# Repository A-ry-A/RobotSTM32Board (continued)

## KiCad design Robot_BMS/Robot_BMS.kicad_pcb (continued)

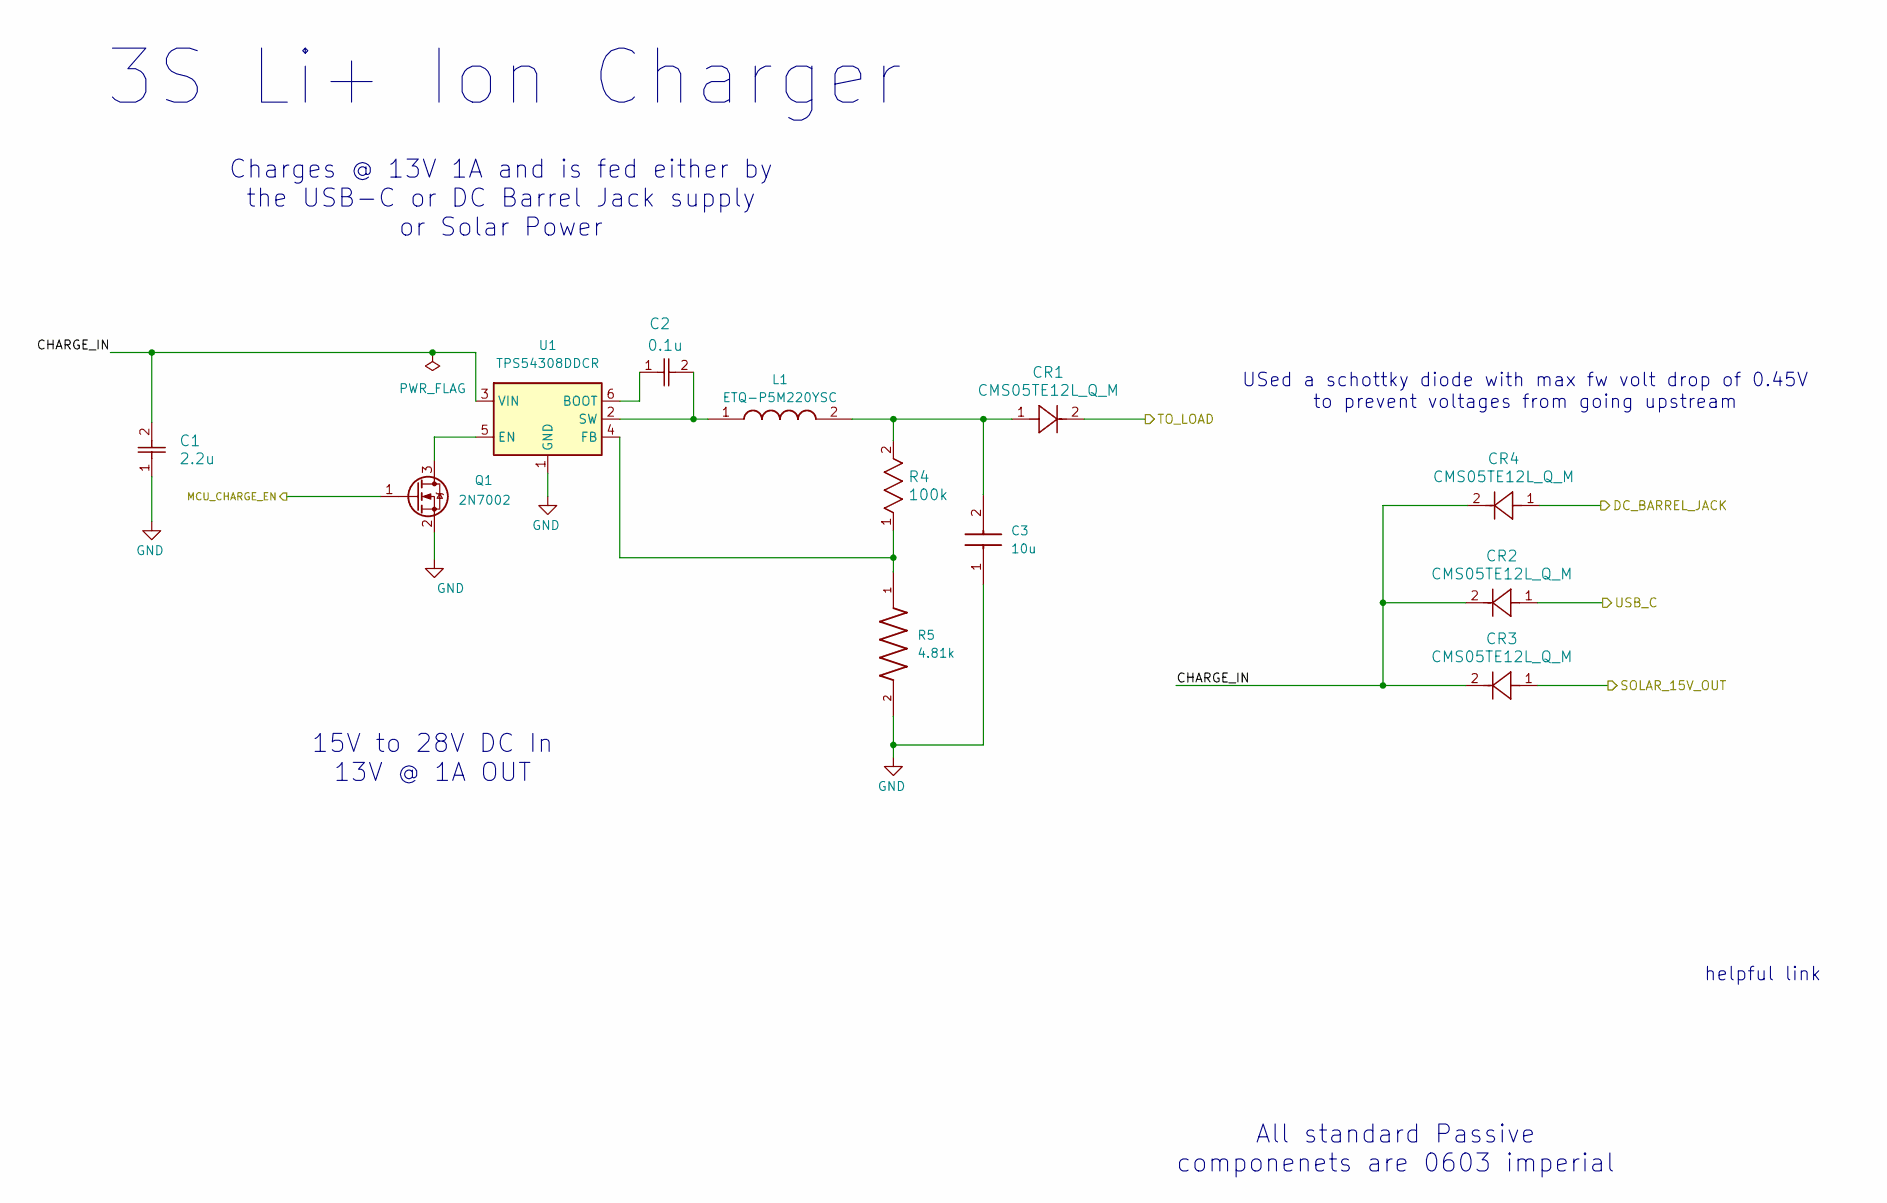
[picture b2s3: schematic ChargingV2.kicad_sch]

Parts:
C1: 2.2u; CAP_GRM188R61H225KE11__MUR; Manufacturer_Part_Number GRM188R61H225KE11D
C2: 0.1u; CAPC17595_87N_KEM; Manufacturer_Part_Number C0603C104K5RACAUTO
C3: 10u; CAPC1608X90N; Mouser Part Number 187-CL10A106MA8NRNC
CR1, CR2, CR3, CR4: CMS05TE12L_Q_M; M-FLAT_TOS; Manufacturer_Part_Number CMS05TE12L_Q_M
L1: ETQ-P5M220YSC; ETQP5M220YSC; Manufacturer_Part_Number ETQ-P5M220YSC
Q1: 2N7002; SOT-23; Manufacturer_Part_Number 2N7002 H6327
R4: 100k; RES_R0603_ROM; Manufacturer_Part_Number ESR03EZPF1003
R5: 4.81k; RESC1608X55N; Manufacturer_Part_Number RN73H1JTTD4811B25
U1: TPS54308DDCR; SOT-23-6; Manufacturer_Part_Number TPS54308DDCR

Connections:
/Charging Circuit/CHARGE_IN: C1.2, CR2.2, CR3.2, CR4.2, U1.3 (VIN)
/Charging Circuit/DC_BARREL_JACK: CR4.1; also elsewhere on the board
/Charging Circuit/MCU_CHARGE_EN: Q1.1 (G); also elsewhere on the board
/Charging Circuit/SOLAR_15V_OUT: CR3.1; also elsewhere on the board
/Charging Circuit/TO_LOAD: CR1.2
/Charging Circuit/USB_C: CR2.1; also elsewhere on the board
GND: C1.1, C3.1, Q1.2 (S), R5.2, U1.1 (GND); also elsewhere on the board
unnamed: C3.2, CR1.1, L1.2, R4.2
unnamed: Q1.3 (D), U1.5 (EN)
unnamed: C2.1, U1.6 (BOOT)
unnamed: R4.1, R5.1, U1.4 (FB)
unnamed: C2.2, L1.1, U1.2 (SW)

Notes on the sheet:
helpful link
Charges @ 13V 1A and is fed either by the USB-C or DC Barrel Jack supply or Solar Power
USed a schottky diode with max fw volt drop of 0.45V to prevent voltages from going upstream
15V to 28V DC In 13V @ 1A OUT
3S Li+ Ion Charger
All standard Passive componenets are 0603 imperial

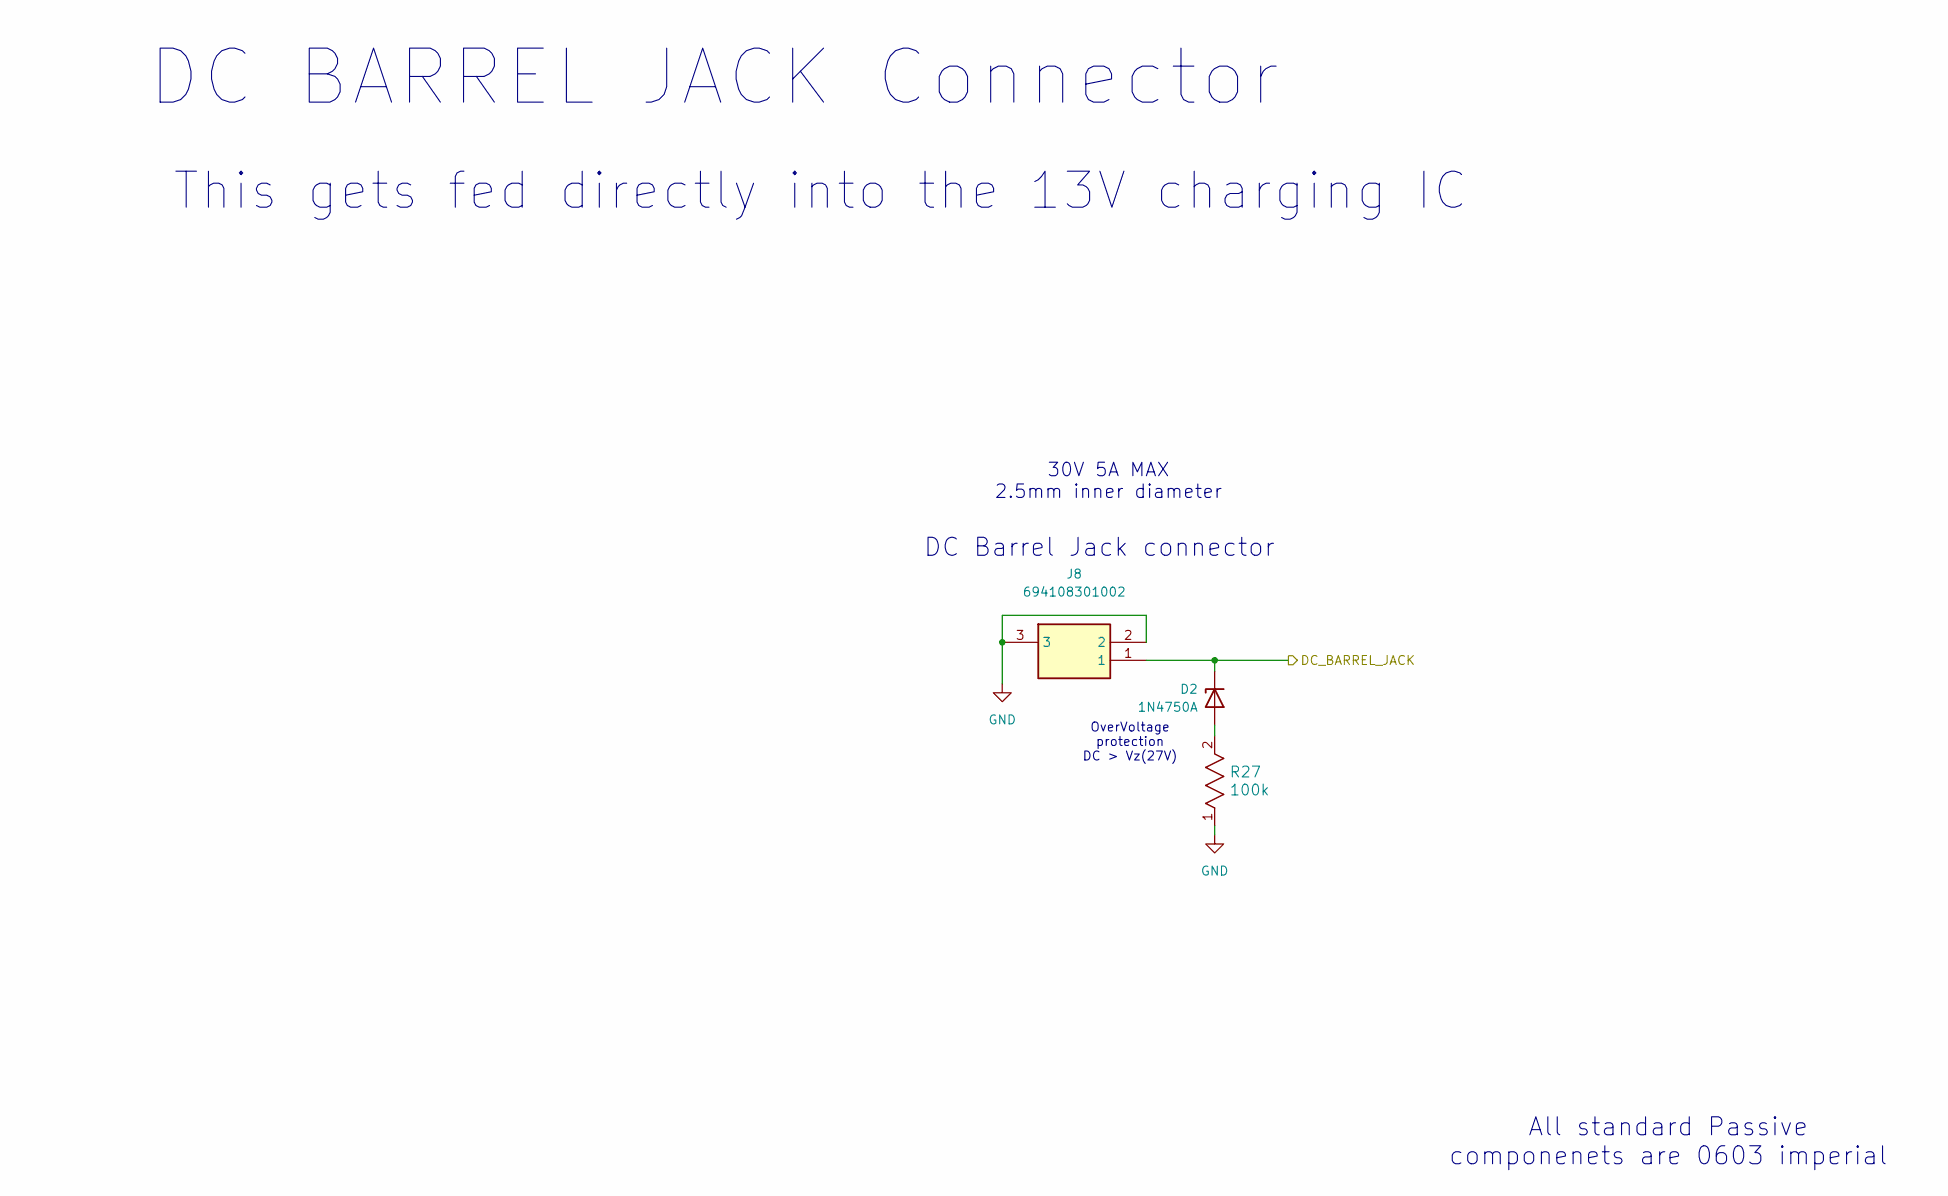
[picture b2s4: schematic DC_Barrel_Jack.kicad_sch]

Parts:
D2: 1N4750A; D_DO-41_SOD81_P10.16mm_Horizontal; Manufacturer_Part_Number 1N4750A
J8: 694108301002; Mouser Part Number 710-694108301002
R27: 100k; RES_R0603_ROM; Manufacturer_Part_Number ESR03EZPF1003

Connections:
/Charging Circuit/DC_BARREL_JACK: D2.1 (K), J8.1; also elsewhere on the board
GND: J8.2, J8.3, R27.1; also elsewhere on the board
unnamed: D2.2 (A), R27.2

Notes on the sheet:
All standard Passive componenets are 0603 imperial
OverVoltage protection DC > Vz(27V)
This gets fed directly into the 13V charging IC
30V 5A MAX 2.5mm inner diameter
DC Barrel Jack connector
DC BARREL JACK Connector

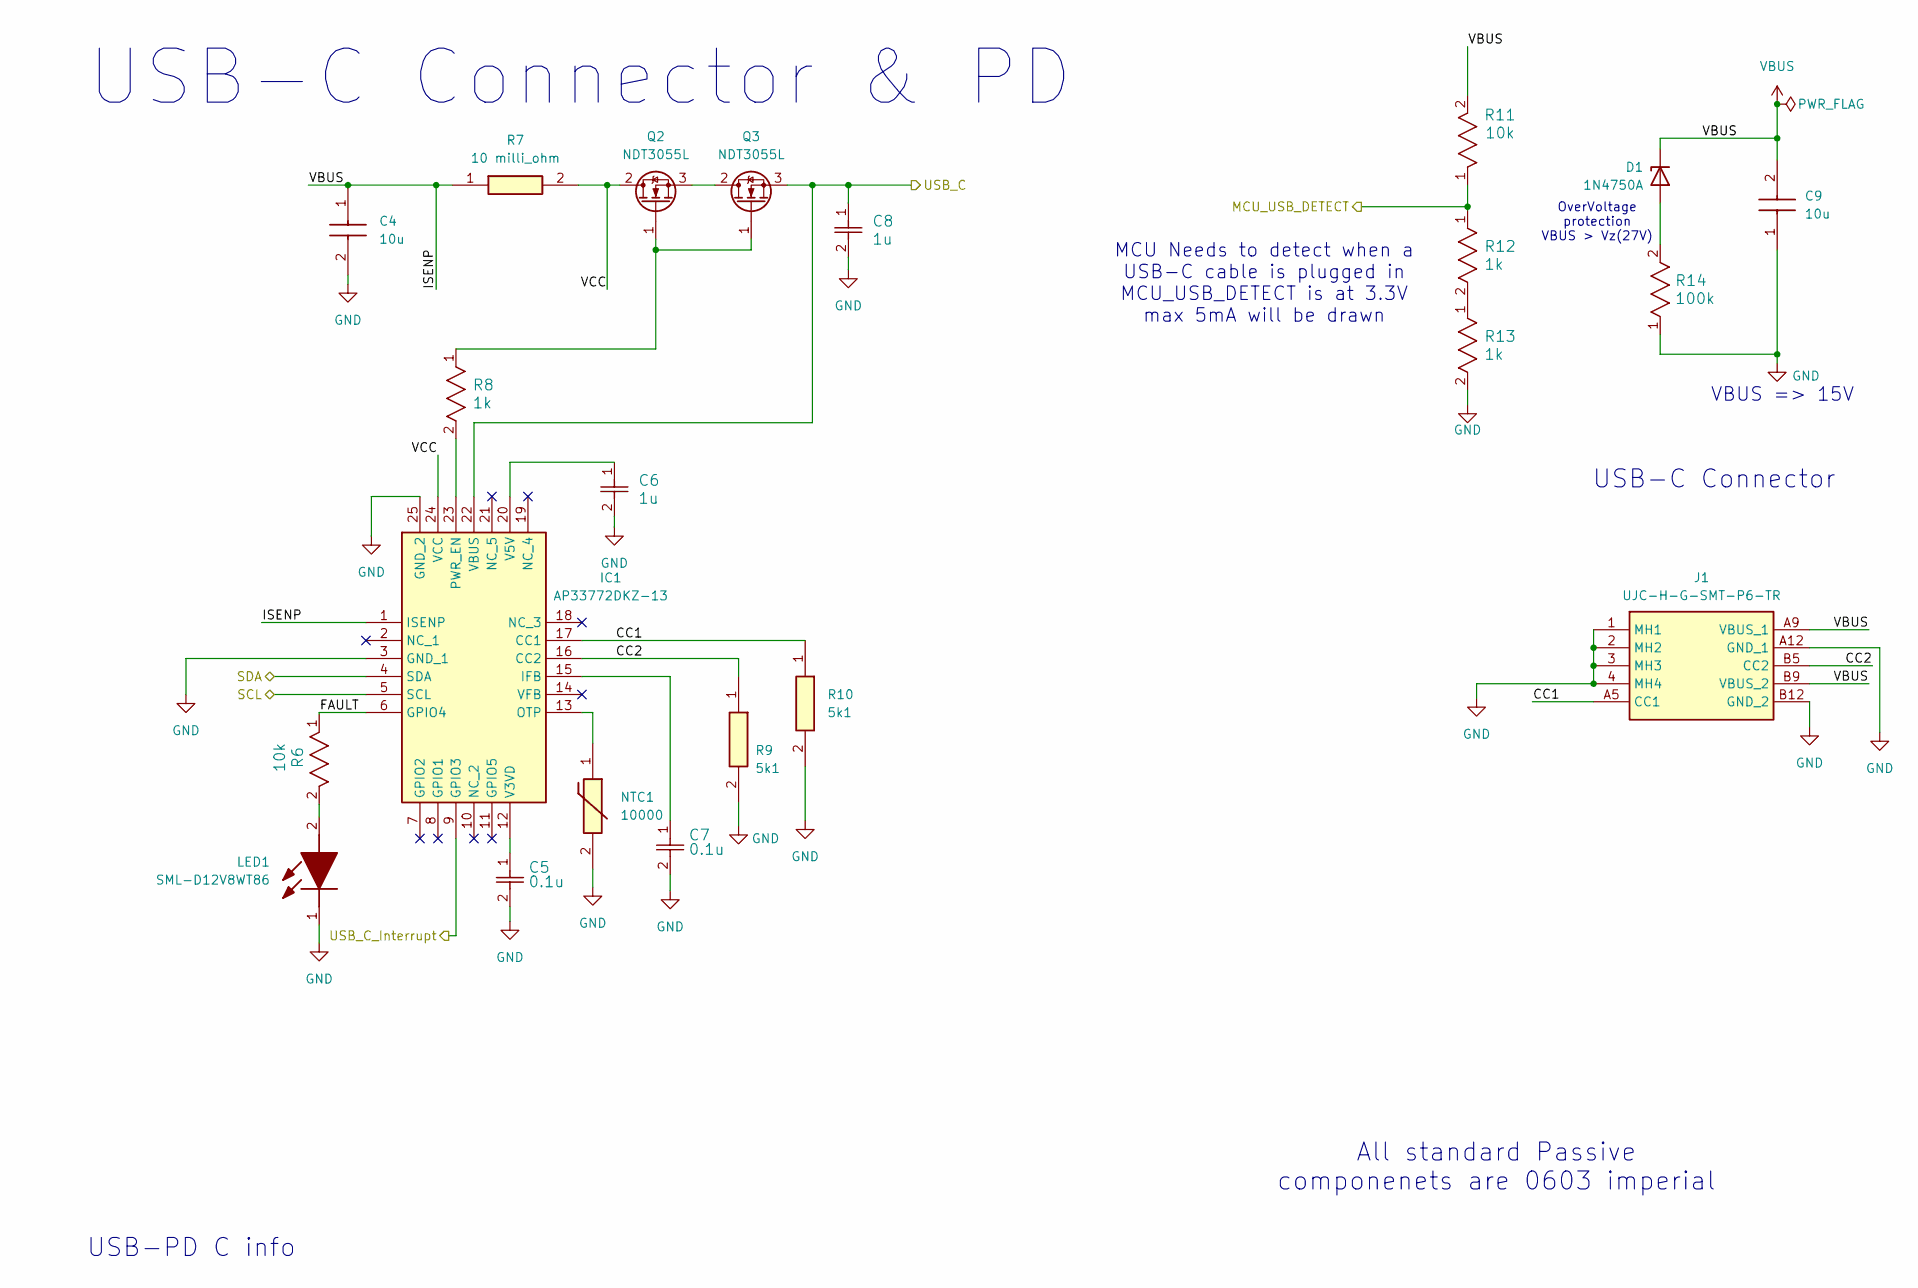
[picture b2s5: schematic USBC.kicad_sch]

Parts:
C4, C9: 10u; CAPC1608X90N; Mouser Part Number 187-CL10A106MA8NRNC
C5, C7: 0.1u; CAPC17595_87N_KEM; Manufacturer_Part_Number C0603C104K5RACAUTO
C6, C8: 1u; CAP_1608_TDK; Manufacturer_Part_Number C1608X5R1H105K080AB
D1: 1N4750A; D_DO-41_SOD81_P10.16mm_Horizontal; Manufacturer_Part_Number 1N4750A
IC1: AP33772DKZ-13; QFN50P400X400X80-25N-D; Mouser Part Number 621-AP33772DKZ-13
J1: UJC-H-G-SMT-P6-TR; UJCHGSMT2P6TR; Mouser Part Number 179-UJCHGSMT2P6TR
LED1: SML-D12V8WT86; SMLD12V8WT86; Mouser Part Number 755-SML-D12V8WT86
NTC1: 10000; THRMC0603X33N; Mouser Part Number 81-NCP03XH103F05RL
Q2, Q3: NDT3055L; SOT-223-3_TabPin2; Manufacturer_Part_Number NDT3055L
R6, R11: 10k; RC0603N_YAG; Manufacturer_Part_Number RC0603FR-0710KL
R7: 10 milli_ohm; RESC1608X60N; Mouser Part Number 660-UR73D1JTTD10L0F
R8, R12, R13: 1k; RES_V0603_VIS; Manufacturer_Part_Number CRCW06031K00JNEAIF
R9, R10: 5k1; ERA3AEB101V; Mouser Part Number 667-ERA-3AED512V
R14: 100k; RES_R0603_ROM; Manufacturer_Part_Number ESR03EZPF1003

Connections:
/Battery Management/SCL: IC1.5 (SCL); also elsewhere on the board
/Battery Management/SDA: IC1.4 (SDA); also elsewhere on the board
/Charging Circuit/USB_C: C8.1, IC1.22 (VBUS), Q3.3 (S); also elsewhere on the board
/To MCU OR System/MCU_USB_DETECT: R11.1, R12.1; also elsewhere on the board
/To MCU OR System/USB_C_Interrupt: IC1.9 (GPIO3); also elsewhere on the board
/USB-C/CC1: IC1.17 (CC1), J1.A5 (CC1), R10.1
/USB-C/CC2: IC1.16 (CC2), J1.B5 (CC2), R9.1
/USB-C/FAULT: IC1.6 (GPIO4), R6.1
/USB-C/VCC: IC1.24 (VCC), Q2.2 (D), R7.2
GND: C4.2, C5.2, C6.2, C7.2, C8.2, C9.1, IC1.3 (GND_1), IC1.25 (GND_2), J1.1 (MH1), J1.2 (MH2), J1.3 (MH3), J1.4 (MH4), J1.A12 (GND_1), J1.B12 (GND_2), LED1.1 (K), NTC1.2, R9.2, R10.2, R13.2, R14.1; also elsewhere on the board
unnamed: D1.2 (A), R14.2
unnamed: C7.1, IC1.15 (IFB)
unnamed: IC1.13 (OTP), NTC1.1
unnamed: IC1.23 (PWR_EN), R8.2
unnamed: C5.1, IC1.12 (V3VD)
unnamed: C6.1, IC1.20 (V5V)
unnamed: LED1.2 (A), R6.2
unnamed: Q2.1 (G), Q3.1 (G), R8.1
unnamed: Q2.3 (S), Q3.2 (D)
unnamed: R12.2, R13.1
VBUS: C4.1, C9.2, D1.1 (K), IC1.1 (ISENP), J1.A9 (VBUS_1), J1.B9 (VBUS_2), R7.1, R11.2

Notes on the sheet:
All standard Passive componenets are 0603 imperial
USB-C Connector & PD
USB-C Connector
VBUS => 15V
USB-PD C info
OverVoltage protection VBUS > Vz(27V)
MCU Needs to detect when a USB-C cable is plugged in MCU_USB_DETECT is at 3.3V max 5mA will be drawn

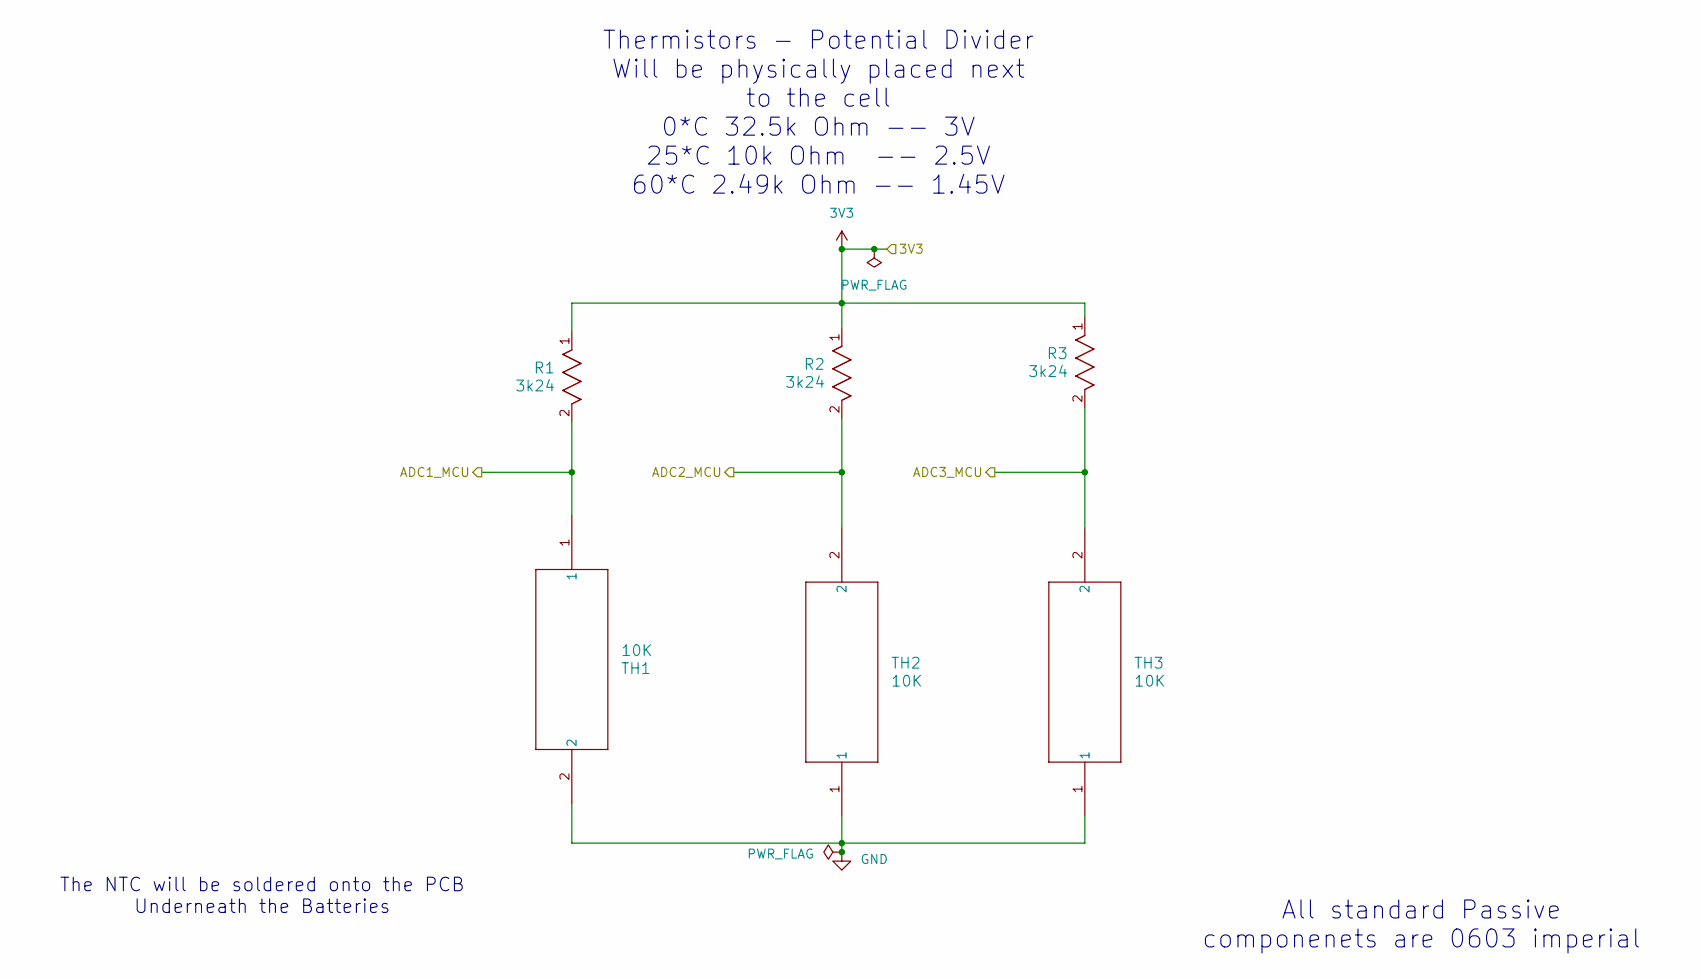
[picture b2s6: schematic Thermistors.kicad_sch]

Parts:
R1, R2, R3: 3k24; RC0603N_YAG; Manufacturer_Part_Number RC0603FR-073K24L
TH1, TH2, TH3: 10K; THERMISTORS_100E3103HB0_VIS; Manufacturer_Part_Number NTCLE100E3103HB0

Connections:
3V3: R1.1, R2.1, R3.1; also elsewhere on the board
/Thermistors/ADC1_MCU: R1.2, TH1.1; also elsewhere on the board
/Thermistors/ADC2_MCU: R2.2, TH2.2; also elsewhere on the board
/Thermistors/ADC3_MCU: R3.2, TH3.2; also elsewhere on the board
GND: TH1.2, TH2.1, TH3.1; also elsewhere on the board

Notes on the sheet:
Thermistors - Potential Divider Will be physically placed next to the cell 0*C 32.5k Ohm -- 3V 25*C 10k Ohm -- 2.5V 60*C 2.49k Ohm -- 1.45V
The NTC will be soldered onto the PCB Underneath the Batteries
All standard Passive componenets are 0603 imperial

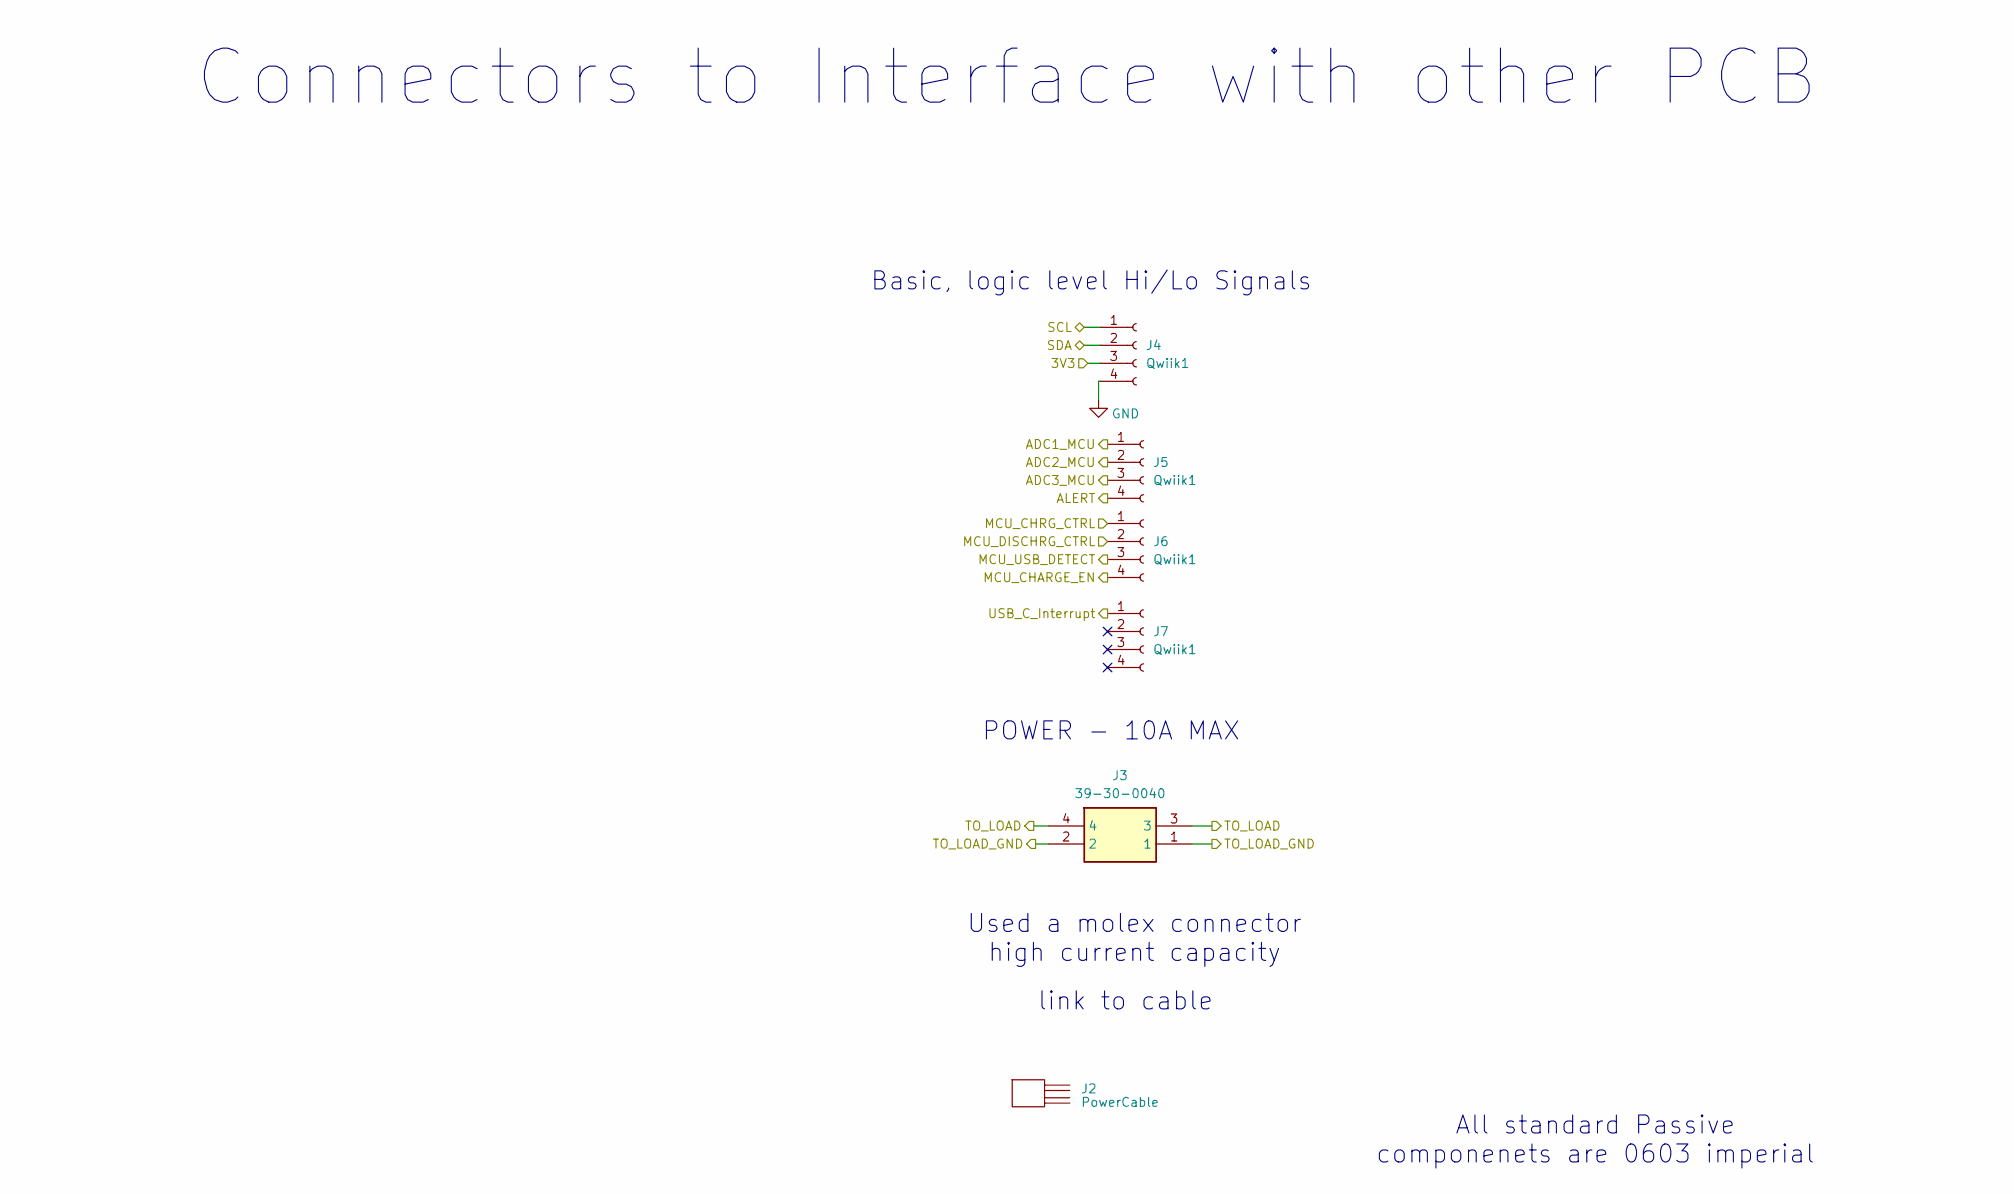
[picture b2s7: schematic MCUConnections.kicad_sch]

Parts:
J2: PowerCable; Manufacturer_Part_Number 45135-0401
J3: 39-30-0040; 39-30-Y040; Mouser Part Number 538-39-30-0040
J4, J5, J6, J7: Qwiik1; JST_SH_BM04B-SRSS-TB_1x04-1MP_P1.00mm_Vertical; Manufacturer_Part_Number SM04B-SRSS-TB(LFSN)

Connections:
3V3: J4.3; also elsewhere on the board
/Battery Management/ALERT: J5.4; also elsewhere on the board
/Battery Management/MCU_CHRG_CTRL: J6.1; also elsewhere on the board
/Battery Management/MCU_DISCHRG_CTRL: J6.2; also elsewhere on the board
/Battery Management/SCL: J4.1; also elsewhere on the board
/Battery Management/SDA: J4.2; also elsewhere on the board
/Battery Management/TO_LOAD: J3.3, J3.4; also elsewhere on the board
/Battery Management/TO_LOAD_GND: J3.1, J3.2; also elsewhere on the board
/Charging Circuit/MCU_CHARGE_EN: J6.4; also elsewhere on the board
/Thermistors/ADC1_MCU: J5.1; also elsewhere on the board
/Thermistors/ADC2_MCU: J5.2; also elsewhere on the board
/Thermistors/ADC3_MCU: J5.3; also elsewhere on the board
/To MCU OR System/MCU_USB_DETECT: J6.3; also elsewhere on the board
/To MCU OR System/USB_C_Interrupt: J7.1; also elsewhere on the board
GND: J4.4; also elsewhere on the board

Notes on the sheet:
All standard Passive componenets are 0603 imperial
POWER - 10A MAX
Basic, logic level Hi/Lo Signals
link to cable
Used a molex connector high current capacity
Connectors to Interface with other PCB

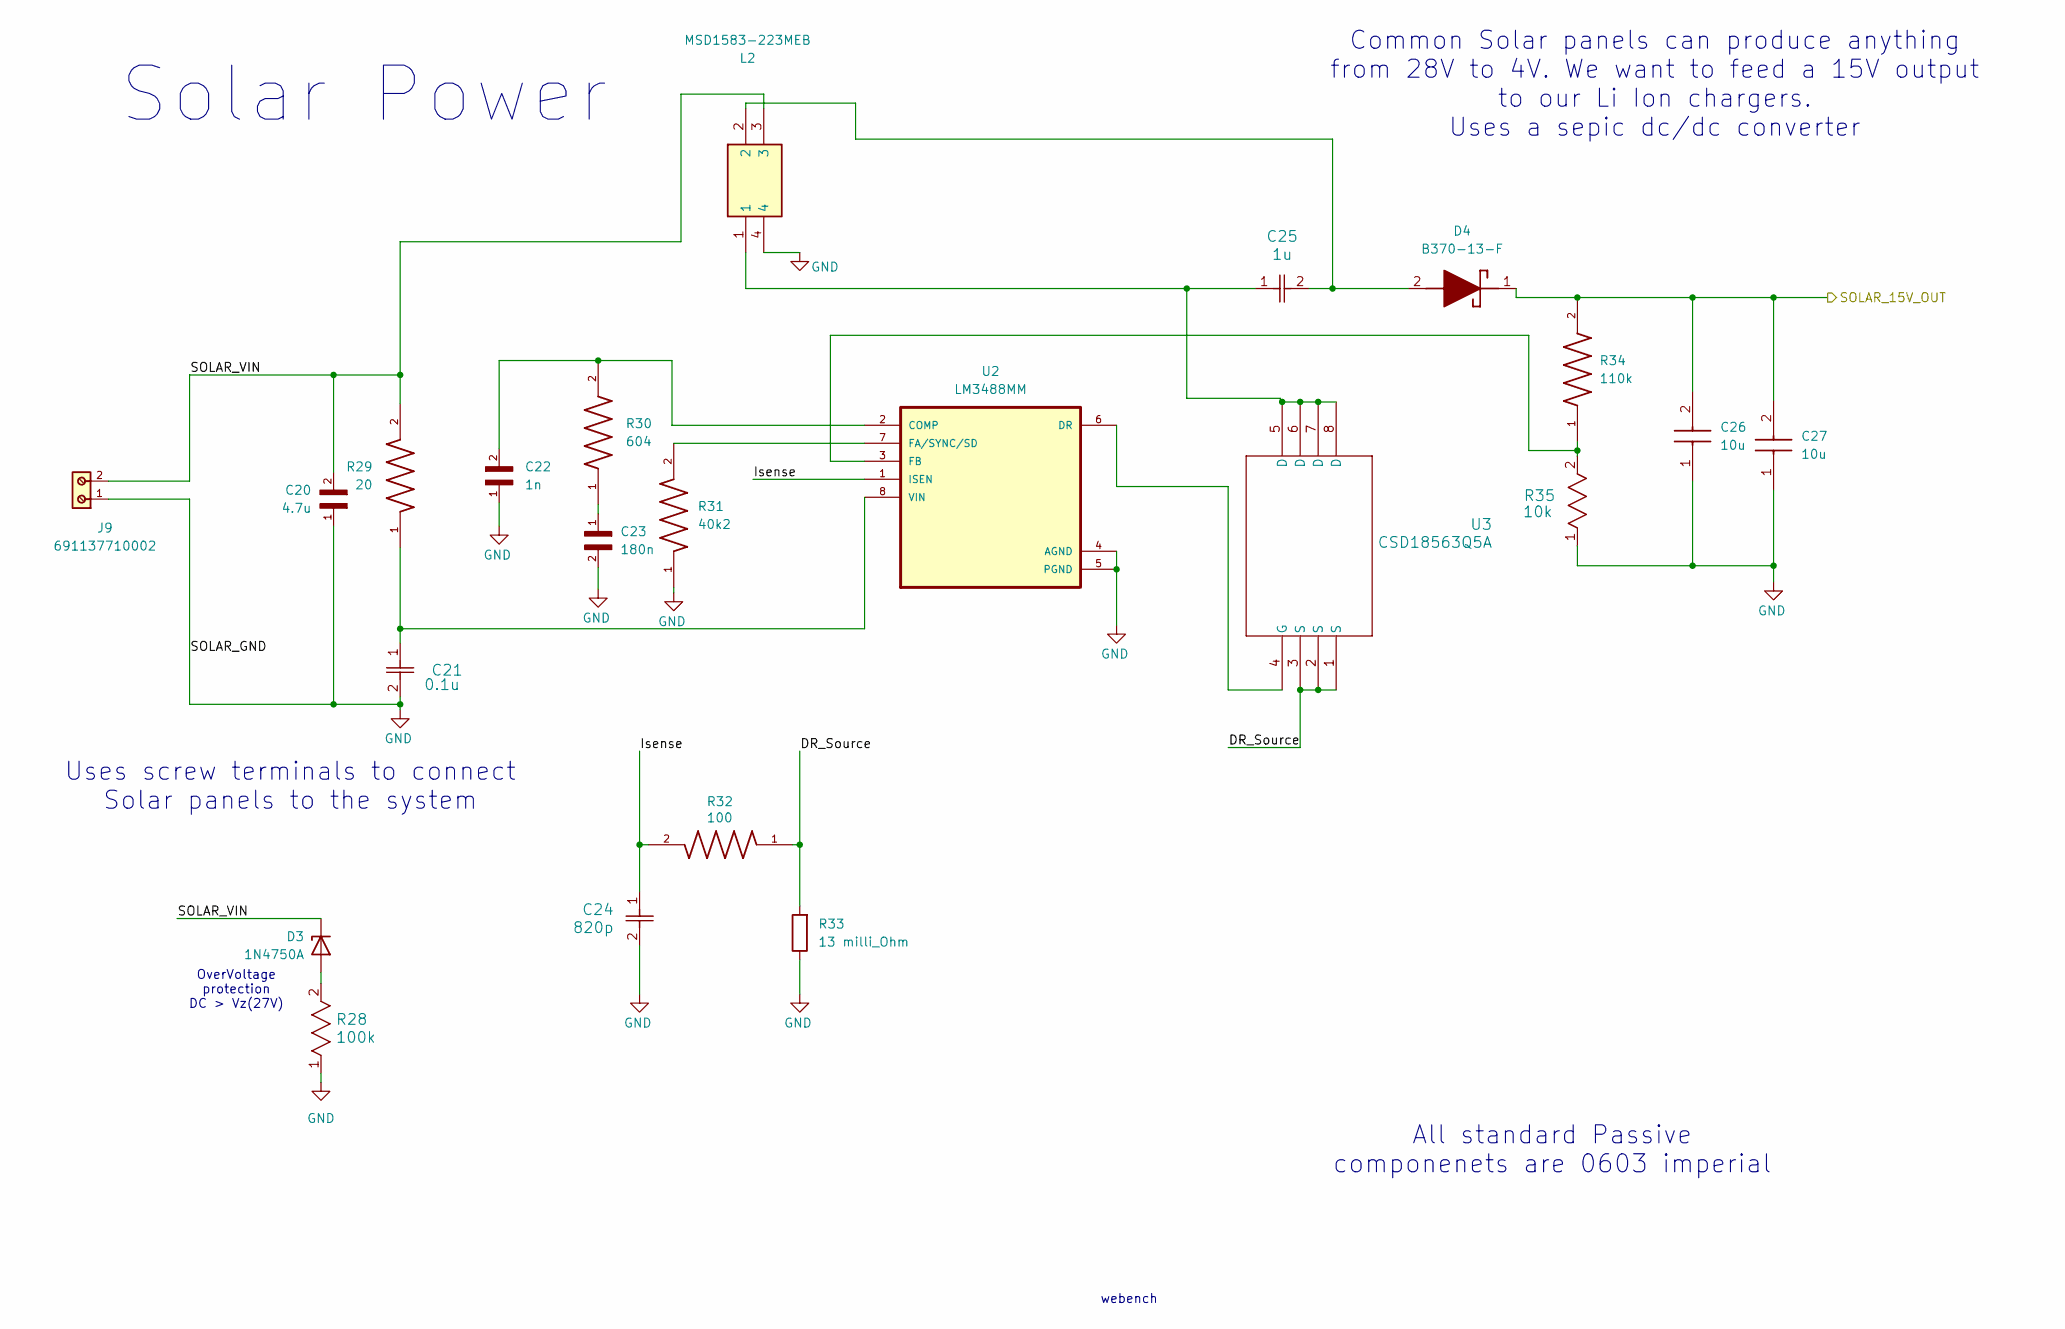
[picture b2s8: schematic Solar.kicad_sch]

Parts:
C20: 4.7u; CAPC1608X120N; Manufacturer_Part_Number ZRB18AR6YA475ME05L
C21: 0.1u; CAPC17595_87N_KEM; Manufacturer_Part_Number C0603C104K5RACAUTO
C22: 1n; CAPRR254W50L508T317H508; PARTREV 081816
C23: 180n; CAPC1608X90; Manufacturer_Part_Number CC0603KRX7R6BB184
C24: 820p; CAPC17795_95N_KEM; Manufacturer_Part_Number C0603X821K5RACAUTO
C25: 1u; CAP_1608_TDK; Manufacturer_Part_Number C1608X5R1H105K080AB
C26, C27: 10u; CAPC1608X90N; Mouser Part Number 187-CL10A106MA8NRNC
D3: 1N4750A; D_DO-41_SOD81_P10.16mm_Horizontal; Manufacturer_Part_Number 1N4750A
D4: B370-13-F; DIOM7959X250N; Mouser Part Number 621-B370-F
J9: 691137710002; Manufacturer_Part_Number 691137710002
L2: MSD1583-223MEB; MSD1583223MEB; Mouser Part Number 994-MSD1583-223MEB
R28: 100k; RES_R0603_ROM; Manufacturer_Part_Number ESR03EZPF1003
R29: 20; RES_ERJPA3F20R0V; PARTREV 3/1/2020
R30: 604; RESC1508X50N; Manufacturer_Part_Number CRCW0603604RFKEA
R31: 40k2; RESC1608X55N; Manufacturer_Part_Number CRCW060340K2FKEAHP
R32: 100; RESC1608X55N; PARTREV V6
R33: 13 milli_Ohm; RESC1508X50N; Manufacturer_Part_Number WFCP0603R0120FE66
R34: 110k; RESC1608X55N; Manufacturer_Part_Number CRCW0603110KFKEAC
R35: 10k; RC0603N_YAG; Manufacturer_Part_Number RC0603FR-0710KL
U2: LM3488MM; SOP65P490X110-8N; Manufacturer_Part_Number LM3488MM
U3: CSD18563Q5A; DQJ8; Manufacturer_Part_Number CSD18563Q5A

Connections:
/Charging Circuit/SOLAR_15V_OUT: C26.2, C27.2, D4.1 (K), R34.2; also elsewhere on the board
/Solar Power/DR_Source: R32.1, R33.2, U3.1 (S), U3.2 (S), U3.3 (S)
/Solar Power/Isense: C24.1, R32.2, U2.1 (ISEN)
/Solar Power/SOLAR_VIN: C20.2, D3.1 (K), J9.2, L2.3, R29.2
GND: C20.1, C21.2, C22.1, C23.2, C24.2, C26.1, C27.1, J9.1, L2.4, R28.1, R31.1, R33.1, R35.1, U2.4 (AGND), U2.5 (PGND); also elsewhere on the board
unnamed: C23.1, R30.1
unnamed: C25.1, L2.1, U3.5 (D), U3.6 (D), U3.7 (D), U3.8 (D)
unnamed: D3.2 (A), R28.2
unnamed: C25.2, D4.2 (A), L2.2
unnamed: C22.2, R30.2, U2.2 (COMP)
unnamed: U2.6 (DR), U3.4 (G)
unnamed: R31.2, U2.7 (FA/SYNC/SD)
unnamed: R34.1, R35.2, U2.3 (FB)
unnamed: C21.1, R29.1, U2.8 (VIN)

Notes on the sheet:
Uses screw terminals to connect Solar panels to the system
OverVoltage protection DC > Vz(27V)
Common Solar panels can produce anything from 28V to 4V. We want to feed a 15V output to our Li Ion chargers. Uses a sepic dc/dc converter
Solar Power
All standard Passive componenets are 0603 imperial
webench

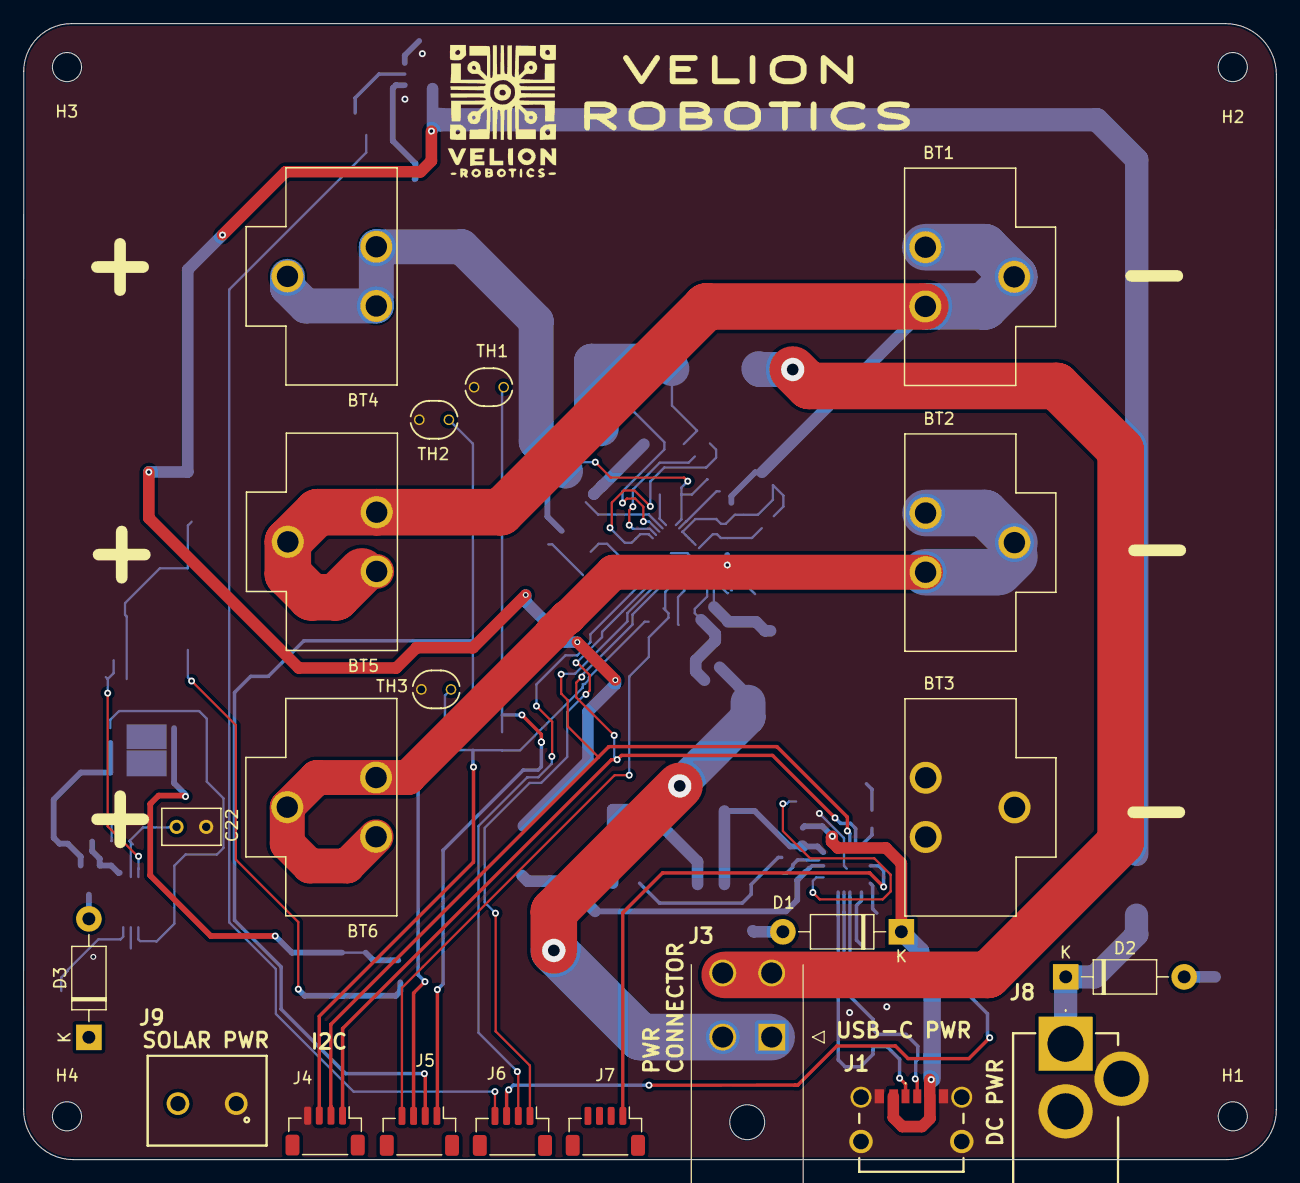
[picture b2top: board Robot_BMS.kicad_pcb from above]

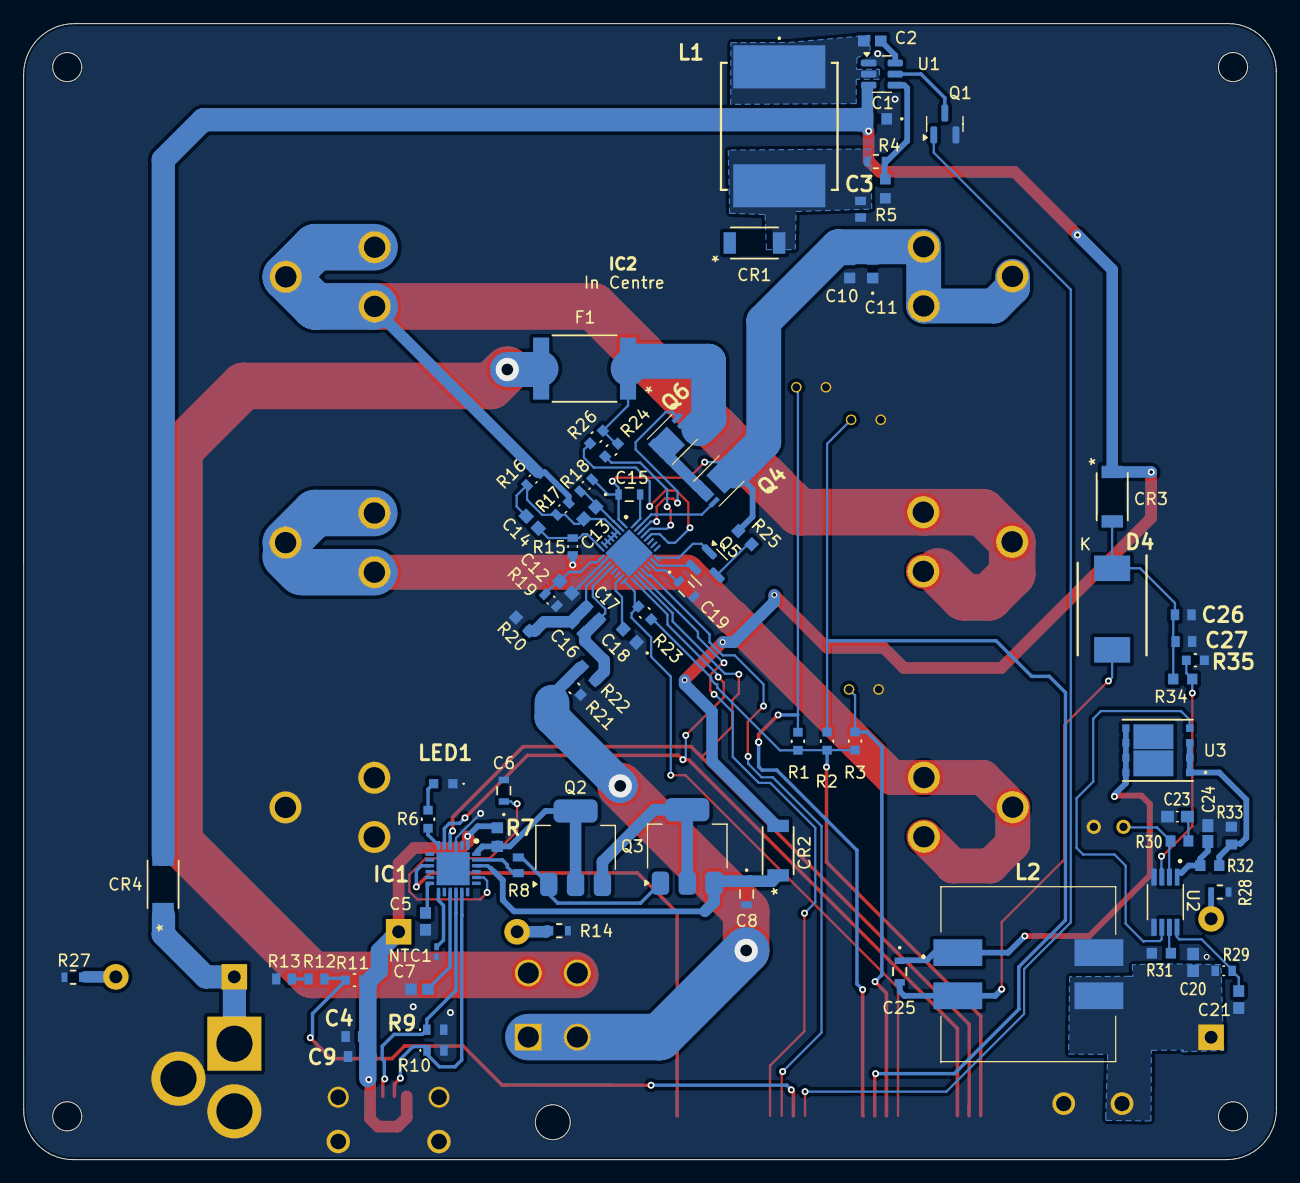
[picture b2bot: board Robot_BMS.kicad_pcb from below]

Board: 2 copper layers, 107.5 x 97.4 mm, 107 parts (82 on the bottom side), 73 nets.
